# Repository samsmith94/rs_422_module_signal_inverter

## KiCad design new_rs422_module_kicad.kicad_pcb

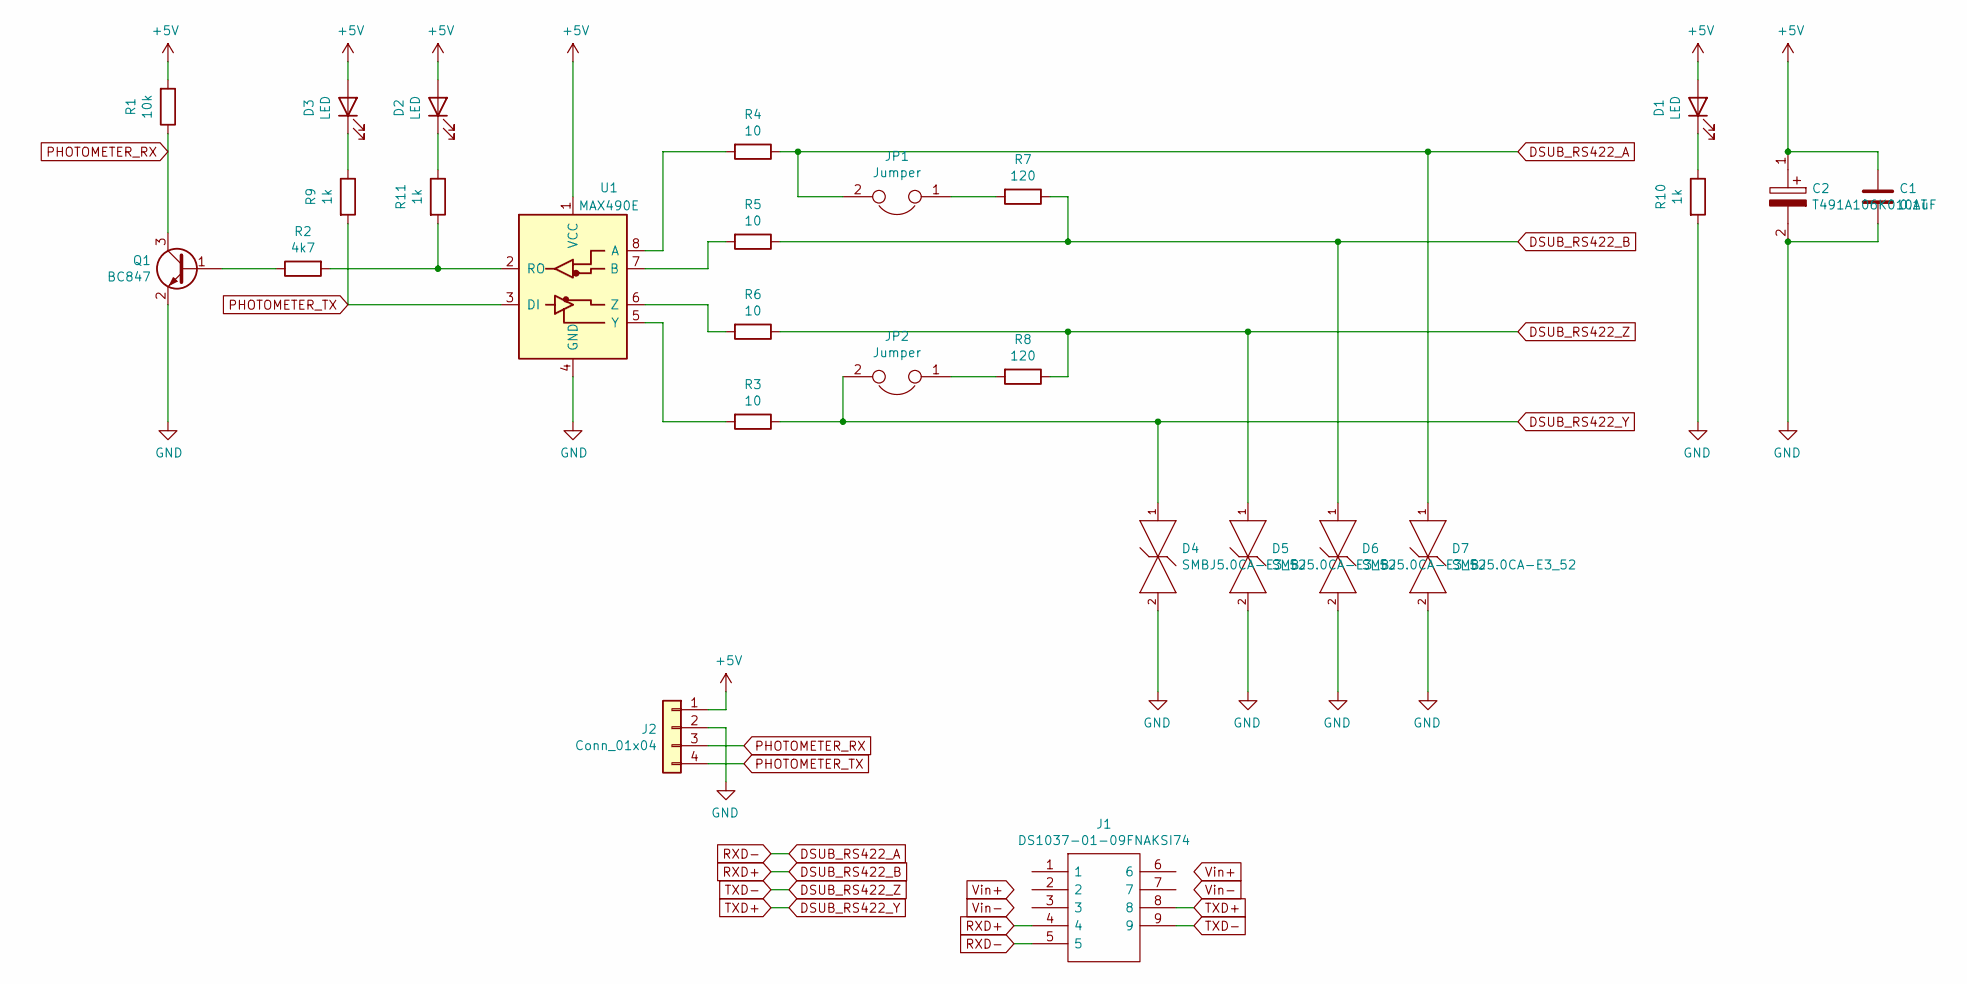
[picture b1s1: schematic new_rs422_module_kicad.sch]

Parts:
C1: 0.1uF; C_0805_2012Metric_Pad1.18x1.45mm_HandSolder
C2: T491A106K010AT; T491A; Manufacturer_Part_Number T491A106K010AT; Mouser Part Number 80-T491A106K010
D1, D2, D3: LED; LED_1206_3216Metric_Pad1.42x1.75mm_HandSolder
D4, D5, D6, D7: SMBJ5.0CA-E3_52; breakdown voltage 6.4V; clamping voltage 9.2V; mouser part number 625-SMBJ5.0CA-E3; digikey description TVS DIODE 5V 9.2V DO214AA
J1: DS1037-01-09FNAKSI74; DS1037_01_09FNAKSI74; Manufacturer_Part_Number DS1037-01-09FNAKSI74
J2: Conn_01x04; PinHeader_1x04_P2.54mm_Vertical
JP1, JP2: Jumper; SolderJumper-2_P1.3mm_Open_TrianglePad1.0x1.5mm
Q1: BC847; SOT-23
R1: 10k; R_1206_3216Metric_Pad1.30x1.75mm_HandSolder
R2: 4k7; R_1206_3216Metric_Pad1.30x1.75mm_HandSolder
R3, R4, R5, R6: 10; R_1206_3216Metric_Pad1.30x1.75mm_HandSolder
R7, R8: 120; R_1206_3216Metric_Pad1.30x1.75mm_HandSolder
R9, R10, R11: 1k; R_1206_3216Metric_Pad1.30x1.75mm_HandSolder
U1: MAX490E; SOIC-8_3.9x4.9mm_P1.27mm

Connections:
+5V: C1.1, C2.1, D1.2 (A), D2.2 (A), D3.2 (A), J2.1, R1.2, U1.1 (VCC)
DSUB_RS422_A: D7.1, J1.5, JP1.2, R4.1
DSUB_RS422_B: D6.1, J1.4, R5.1, R7.1
DSUB_RS422_Y: D4.1, J1.8, JP2.2, R3.1
DSUB_RS422_Z: D5.1, J1.9, R6.1, R8.1
GND: C1.2, C2.2, D4.2, D5.2, D6.2, D7.2, J2.2, Q1.2 (E), R10.2, U1.4 (GND)
unnamed: D1.1 (K), R10.1
unnamed: D2.1 (K), R11.1
unnamed: D3.1 (K), R9.1
unnamed: JP1.1, R7.2
unnamed: JP2.1, R8.2
unnamed: Q1.1 (B), R2.1
unnamed: R3.2, U1.5 (Y)
unnamed: R4.2, U1.8 (A)
unnamed: R5.2, U1.7 (B)
unnamed: R6.2, U1.6 (Z)
unnamed: R2.2, R11.2, U1.2 (RO)
PHOTOMETER_RX: J2.3, Q1.3 (C), R1.1
PHOTOMETER_TX: J2.4, R9.2, U1.3 (DI)

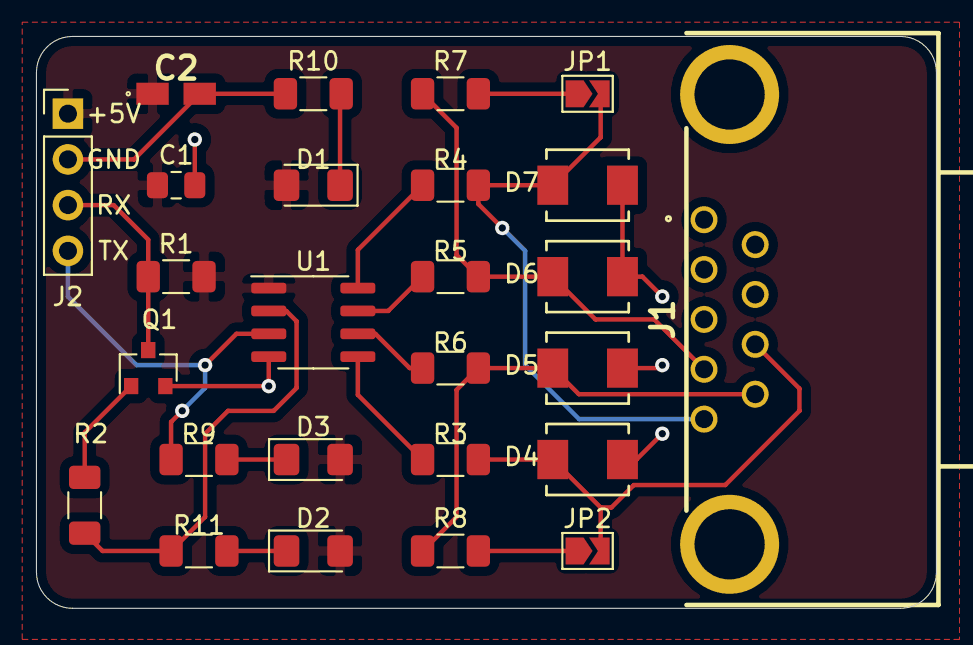
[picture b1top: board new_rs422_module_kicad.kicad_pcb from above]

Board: 2 copper layers, 50.0 x 31.8 mm, 26 parts (0 on the bottom side), 19 nets.

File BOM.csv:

Azonosító,Jelölés,Csomag,Mennyiség,Elnevezés,Szállító és referencia
2,"D7,D6,D5,D4",SMBJ5.0CA-E3_52,4,SMBJ5.0CA-E3_52,https://hu.farnell.com/vishay/smbj5-0ca-e3-52/diode-tvs-600w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
3,C2,T491A,1,T491A106K010AT,https://hu.farnell.com/kemet/t491a106k010at/cap-10-f-10v-10-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
4,J2,PinHeader_1x04_P2.54mm_Vertical,1,Conn_01x04,"nem kell csatlakozó, mert inkább forrasszunk kábelt"
5,J1,DS1037_01_09FNAKSI74,1,DS1037-01-09FNAKSI74,https://www.hestore.hu/prod_10040587.html
6,U1,SOIC-8_3.9x4.9mm_P1.27mm,1,MAX490E,https://hu.farnell.com/maxim-integrated-products/max490esa-t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
7,"R11,R10,R9",R_1206_3216Metric_Pad1.30x1.75mm_HandSolder,3,1k,https://www.hestore.hu/prod_10000256.html
8,"R8,R7",R_1206_3216Metric_Pad1.30x1.75mm_HandSolder,2,120,https://www.hestore.hu/prod_10035936.html
9,"R6,R5,R4,R3",R_1206_3216Metric_Pad1.30x1.75mm_HandSolder,4,10,https://www.hestore.hu/prod_10000781.html
10,R2,R_1206_3216Metric_Pad1.30x1.75mm_HandSolder,1,4k7,https://www.hestore.hu/prod_10000299.html
11,R1,R_1206_3216Metric_Pad1.30x1.75mm_HandSolder,1,10k,https://www.hestore.hu/prod_10000297.html
12,Q1,SOT-23,1,BC847,https://www.hestore.hu/prod_10020906.html
13,"D3,D2,D1",LED_1206_3216Metric_Pad1.42x1.75mm_HandSolder,3,LED,https://www.hestore.hu/prod_10034481.html
14,C1,C_0805_2012Metric_Pad1.18x1.45mm_HandSolder,1,0.1uF,https://www.hestore.hu/prod_10001122.html
,,,,,
,,,,,
,,,,,EGYÉB:
,,,,,https://www.hestore.hu/prod_10023204.html
,,,,,https://www.hestore.hu/prod_10030084.html

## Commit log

2022-10-05 init existing project
2022-10-05 done & gerbers generated
2022-10-05 PnP, BOM
